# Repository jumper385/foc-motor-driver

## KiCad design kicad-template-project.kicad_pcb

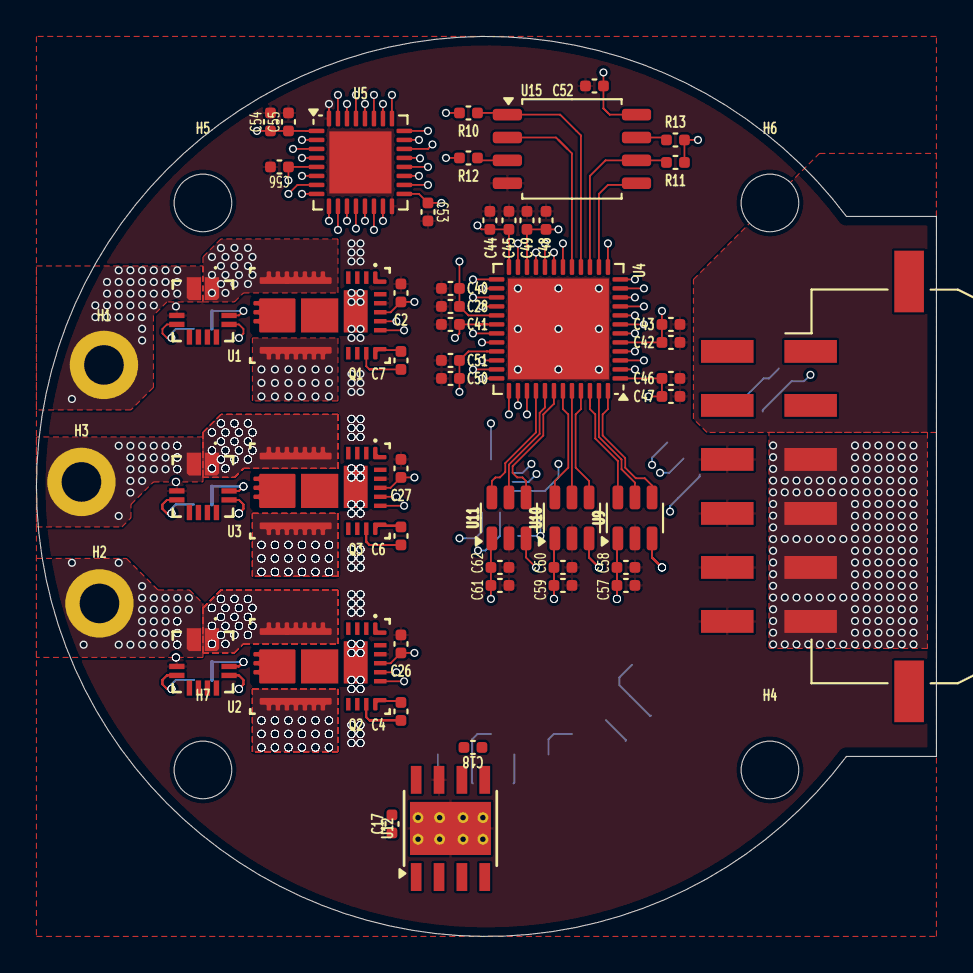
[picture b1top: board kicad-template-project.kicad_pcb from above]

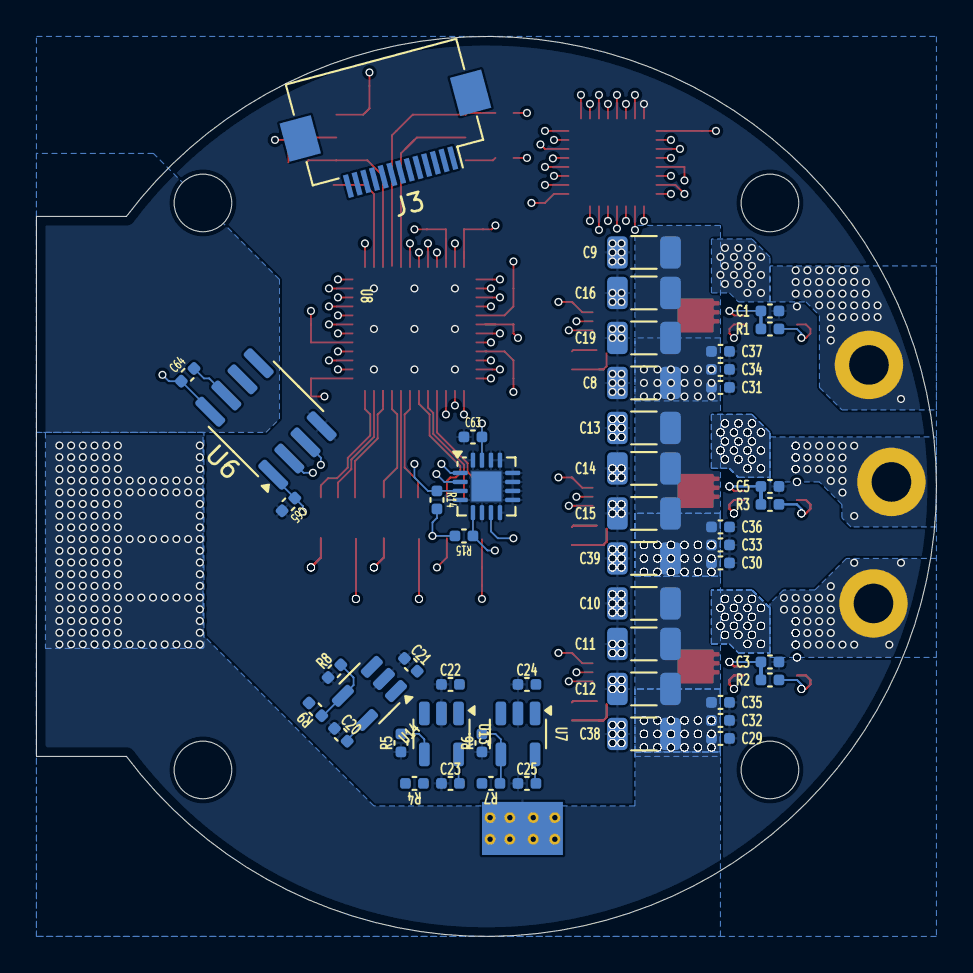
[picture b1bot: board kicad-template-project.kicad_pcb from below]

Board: 6 copper layers, 50.0 x 50.0 mm, 107 parts (50 on the bottom side), 63 nets.

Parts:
C1, C2, C3, C4, C5, C6, C7, C17, C26, C27, C28, C29, C30, C31, C32, C33, C34, C35, C36, C37, C41, C42, C45, C47, C49, C51, C52, C53, C55, C56, C57, C59, C61, C64, C65: 100 nF; C_0402
C8, C9, C10, C11, C12, C13, C14, C15, C16, C19, C38, C39: C; C_1206_3216Metric
C18, C20, C21, C22, C23, C24, C25, C58, C60, C62, C63: 1 uF; C_0402
C40, C43, C44, C46, C48, C50, C54: 4.7uF; C_0402
H1, H2, H3: MountingHole_Pad; MountingHole_2.2mm_M2_DIN965_Pad
H4, H5, H6, H7: MountingHole; MountingHole_3.2mm_M3
J2: Conn_01x12; Molex_Micro-Fit_3.0_43045-1210_2x06-1MP_P3.00mm_Horizontal
J3: Conn_01x13; Hirose_FH12-13S-0.5SH_1x13-1MP_P0.50mm_Horizontal
Q1, Q2, Q3: LMG2100R026; VBN0018A-MFG
R1, R2, R3, R4, R5, R6, R7, R8, R9, R10, R11, R12, R13, R14, R15: 10K; R_0402
U1, U2, U3: MCS1823; MPS_MCS1823_TQFN-12_MNP
U4: ICE40UP5K-SG48ITR; QFN-48-1EP_7x7mm_P0.5mm_EP5.6x5.6mm
U5: STM32L432KBUx; QFN-32-1EP_5x5mm_P0.5mm_EP3.45x3.45mm
U6: ISO1044BD; SOIC-8_3.9x4.9mm_P1.27mm
U7, U13, U14: MIC5219YM5; SOT-23-5
U8: MLX90395xLW; QFN-16-1EP_3x3mm_P0.5mm_EP1.675x1.675mm
U9, U10, U11: ADCS7476; SOT-23-6
U12: TPS54360DDA; TI_SO-PowerPAD-8_ThermalVias
U15: W25Q16JVSS; SOIC-8_5.3x5.3mm_P1.27mm

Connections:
/CAN/CAN_RX: U5.21 (CAN1_RX), U6.3 (RXD)
/CAN/CAN_TX: U5.22 (CAN1_TX), U6.2 (TXD)
/FPGA/ADC0_CS: U4.46 (IOB_0a), U9.6 (CS)
/FPGA/ADC0_SCLK: U4.48 (IOB_4a), U9.4 (SCLK)
/FPGA/ADC0_SDATA: U4.47 (IOB_2a), U9.5 (SDATA)
/FPGA/ADC1_CS: U4.43 (IOT_49a), U10.6 (CS)
/FPGA/ADC1_SCLK: U4.45 (IOB_5b), U10.4 (SCLK)
/FPGA/ADC1_SDATA: U4.44 (IOB_3b_G6), U10.5 (SDATA)
/FPGA/ADC2_CS: U4.40 (RGB1), U11.6 (CS)
/FPGA/ADC2_SCLK: U4.42 (IOT_51a), U11.4 (SCLK)
/FPGA/ADC2_SDATA: U4.41 (RGB2), U11.5 (SDATA)
/FPGA/FLASH_CLK: R11.1, U4.15 (IOB_34a_SPI_SCK), U15.6 (CLK)
/FPGA/FLASH_CS: R10.1, U4.16 (IOB_35b_SPI_SS), U15.1 (~CS)
/FPGA/FLASH_MISO: U4.17 (IOB_33b_SPI_SI), U15.2 (DO/IO_{1})
/FPGA/FLASH_MOSI: U4.14 (IOB_32a_SPI_SO), U15.5 (DI/IO_{0})
/FPGA/ISNS0: U2.11 (VOUT), U9.3 (VIN)
/FPGA/ISNS1: U1.11 (VOUT), U10.3 (VIN)
/FPGA/ISNS2: U3.11 (VOUT), U11.3 (VIN)
/FPGA/PH0_OCD: R1.1, U1.6 (OCD), U4.27 (IOT_38b)
/FPGA/PH0_PWM_HI: Q1.12 (HI), U4.26 (IOT_39a)
/FPGA/PH0_PWM_LI: Q1.13 (LI), U4.25 (IOT_36b)
/FPGA/PH1_OCD: R2.1, U2.6 (OCD), U4.34 (IOT_44b)
/FPGA/PH1_PWM_HI: Q2.12 (HI), U4.36 (IOT_48b)
/FPGA/PH1_PWM_LI: Q2.13 (LI), U4.35 (IOT_46b_G0)
/FPGA/PH2_OCD: R3.1, U3.6 (OCD), U4.28 (IOT_41a)
/FPGA/PH2_PWM_HI: Q3.12 (HI), U4.32 (IOT_43a)
/FPGA/PH2_PWM_LI: Q3.13 (LI), U4.31 (IOT_42b)
/FPGA/SPI_MISO: U4.21 (IOB_23b), U5.12 (SPI1_MISO)
/FPGA/SPI_MOSI: U4.23 (IOT_37a), U5.13 (SPI1_MOSI)
/FPGA/SPI_SCK: U4.20 (IOB_25b_G3), U5.11 (SPI1_SCK)
/MAG/I2C_SCL: R14.1, U5.19 (I2C1_SCL), U8.3 (SCL)
/MAG/I2C_SDA: R15.1, U5.20 (I2C1_SDA), U8.5 (SDA)
/PH0/HB_SW: Q1.5 (SW), U1.1 (IP+)
/PH0/PH_OUT: H1.1, U1.3 (IP-)
/PH1/HB_SW: Q2.5 (SW), U2.1 (IP+)
/PH1/PH_OUT: H2.1, U2.3 (IP-)
/PH2/HB_SW: Q3.5 (SW), U3.1 (IP+)
/PH2/PH_OUT: H3.1, U3.3 (IP-)
GND: C1.1, C2.1, C3.1, C5.1, C8.2, C9.2, C10.2, C11.2, C12.2, C13.2, C14.2, C15.2, C16.2, C19.2, C20.1, C21.1, C22.1, C23.1, C24.1, C25.1, C26.1, C27.1, C28.2, C29.2, C30.2, C31.2, C32.2, C33.2, C34.2, C35.2, C36.2, C37.2, C38.2, C39.2, C40.2, C41.2, C42.2, C43.2, C44.2, C45.2, C46.2, C47.2, C48.2, C49.2, C50.2, C51.2, C52.1, C53.2, C54.2, C55.2, C56.2, C57.1, C58.1, C59.1, C60.1, C61.1, C62.1, C63.1, C65.2, J2.9, J2.10, J2.11, J2.12, Q1.6 (PGND), Q1.15 (AGND), Q1.17 (PGND), Q1.18 (PGND), Q2.6 (PGND), Q2.15 (AGND), Q2.17 (PGND), Q2.18 (PGND), Q3.6 (PGND), Q3.15 (AGND), Q3.17 (PGND), Q3.18 (PGND), R5.1, R6.1, R8.1, U1.5 (GND), U2.5 (GND), U3.5 (GND), U4.49 (GND), U5.16 (VSS), U5.32 (VSS), U5.33 (VSS), U6.4 (GND1), U7.2 (GND), U8.4 (V_{SS}), U8.6 (MISO), U8.8 (V_{SS}), U8.9 (V_{SS}), U8.10 (V_{SS}), U8.11 (A1), U8.12 (A0), U8.13 (V_{SS}), U8.14 (V_{SS}), U8.16 (V_{SS}), U8.17 (V_{SS}), U9.2 (GND), U10.2 (GND), U11.2 (GND), U12.7 (GND), U12.9 (GNDPAD), U13.2 (GND), U14.2 (GND), U15.4 (GND)
ISO_3V3: C64.1, U6.8 (VCC2)
ISO_GND: C64.2, U6.7 (GND2)
unnamed: C17.2, U12.8 (SW)
unnamed: C7.1, Q1.10 (HB)
unnamed: C7.2, Q1.11 (HS)
unnamed: C4.1, Q2.10 (HB)
unnamed: C4.2, Q2.11 (HS)
unnamed: C6.1, Q3.10 (HB)
unnamed: C6.2, Q3.11 (HS)
unnamed: R6.2, R7.1, U7.4 (ADJ)
unnamed: C57.2, C58.2, U9.1 (VDD)
unnamed: C59.2, C60.2, U10.1 (VDD)
unnamed: C61.2, C62.2, U11.1 (VDD)
unnamed: C17.1, U12.1 (BOOT)
unnamed: R4.1, R5.2, U13.4 (ADJ)
unnamed: R8.2, R9.1, U14.4 (ADJ)
unnamed: R13.1, U15.7 (~HOLD/~RESET/IO_{3})
unnamed: R12.1, U15.3 (~WP/IO_{2})
VDD_1V2: C41.1, C42.1, C43.1, U4.5 (VCC), U4.30 (VCC)
VDD_2V5: C20.2, R9.2, U14.5 (OUT)
VDD_3V3: C1.2, C3.2, C5.2, C25.2, C28.1, C40.1, C44.1, C45.1, C46.1, C47.1, C48.1, C49.1, C50.1, C51.1, C52.2, C53.1, C54.1, C55.1, C56.1, C63.2, C65.1, R1.2, R2.2, R3.2, R7.2, R10.2, R11.2, R12.2, R13.2, R14.2, R15.2, U1.12 (VCC), U2.12 (VCC), U3.12 (VCC), U4.1 (VCCIO_2), U4.22 (SPI_VCCIO1), U4.24 (VPP_2V5), U4.29 (VCCPLL), U4.33 (VCCIO_0), U5.1 (VDD), U5.5 (VDDA), U5.17 (VDD), U6.1 (VCC1), U7.5 (OUT), U8.2 (MS), U8.15 (V_{DD}), U15.8 (VCC)
VDD_5V: C2.2, C23.2, C26.2, C27.2, Q1.14 (VCC), Q2.14 (VCC), Q3.14 (VCC), R4.2, U13.5 (OUT)
VDD_6V: C18.1, C21.2, C22.2, C24.2, U7.1 (IN), U7.3 (EN), U13.1 (IN), U13.3 (EN), U14.1 (IN), U14.3 (EN)
VDD_48V: C8.1, C9.1, C10.1, C11.1, C12.1, C13.1, C14.1, C15.1, C16.1, C19.1, C29.1, C30.1, C31.1, C32.1, C33.1, C34.1, C35.1, C36.1, C37.1, C38.1, C39.1, J2.3, J2.4, J2.5, J2.6, Q1.7 (VIN), Q2.7 (VIN), Q3.7 (VIN), U12.2 (VIN)

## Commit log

2026-04-22 chore: update lib
2026-04-22 feat: initial layout
2026-04-22 fix: adjusted positining
2026-04-22 fix: added commitizen
2026-04-22 bump: version 0.0.1 → 0.1.0
2026-04-22 fix: added switcher placeholders
2026-04-22 bump: version 0.1.0 → 0.1.1
2026-04-23 feat: done rough board placements for general shape
2026-04-23 bump: version 0.1.1 → 0.2.0
2026-04-23 ci: updated release outputs
2026-04-23 ci: update build
2026-04-23 fix: update fpga with power supply
2026-04-23 bump: version 0.2.0 → 0.2.1
2026-04-23 fix: added placeholder stlink connector
2026-04-23 ci: fix output name
2026-04-23 bump: version 0.2.1 → 0.2.2
2026-04-24 fix: adjusting positioning of programmign header
2026-04-24 fix: fleshignout schematic for mcu, fpga and mag + peripherals
2026-04-24 bump: version 0.2.2 → 0.2.3
2026-04-24 fix: finalized position of fpc programmer
2026-04-24 bump: version 0.2.3 → 0.2.4
